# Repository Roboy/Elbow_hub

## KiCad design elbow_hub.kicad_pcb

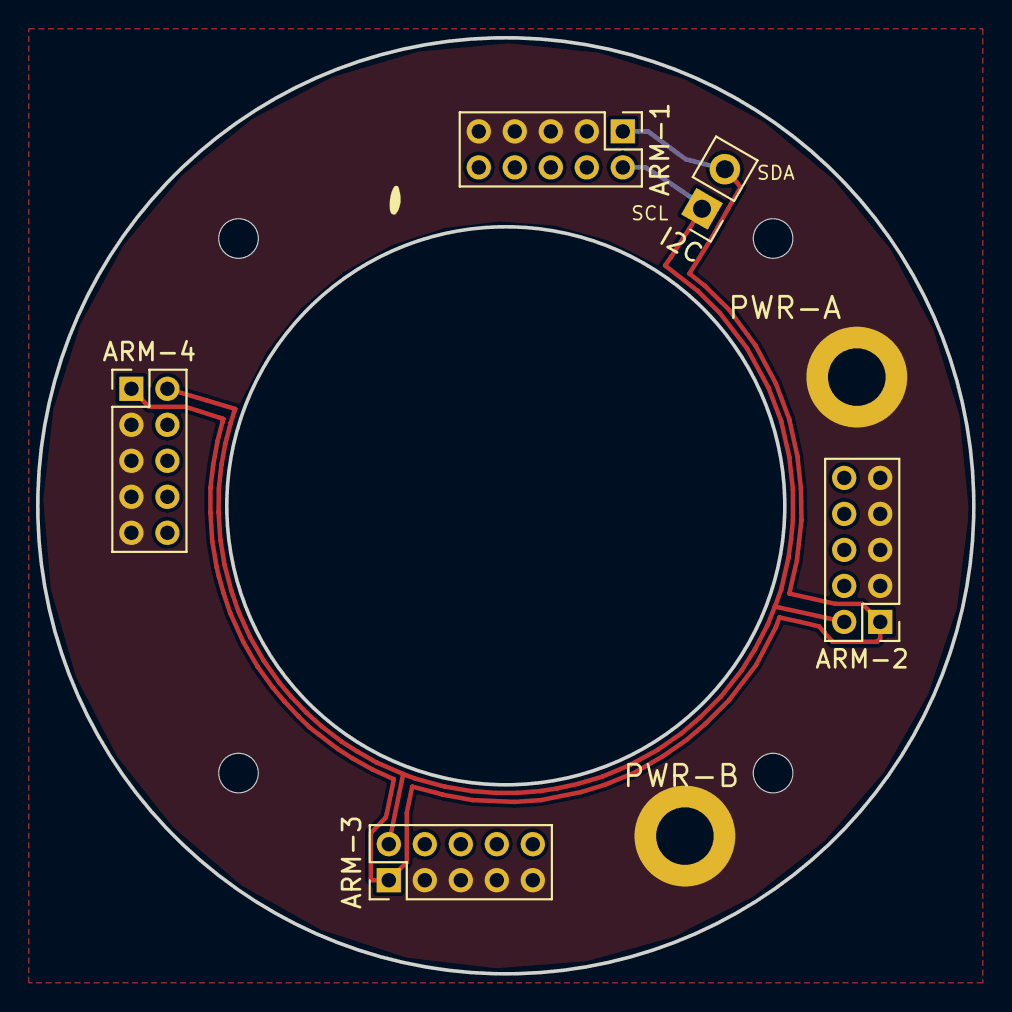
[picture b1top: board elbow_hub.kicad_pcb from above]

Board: 2 copper layers, 52.0 x 52.0 mm, 11 parts (0 on the bottom side), 4 nets.

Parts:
ARM-1, ARM-2, ARM-3, ARM-4: Conn_02x05_Odd_Even; PinHeader_2x05_P2.00mm_Vertical
I2C: Conn_01x02; PinHeader_1x02_P2.54mm_Vertical
MK1, MK2, MK3, MK4: M2; MountingHole_2.2mm_M2_DIN965
PWR-A: Conn_01x01; MountingHole_3.2mm_M3_DIN965_Pad
PWR-B: Conn_01x01; MountingHole_3.2mm_M3_DIN965_Pad

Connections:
+5V: ARM-1.4, ARM-1.6, ARM-1.8, ARM-1.10, ARM-2.4, ARM-2.6, ARM-2.8, ARM-2.10, ARM-3.4, ARM-3.6, ARM-3.8, ARM-3.10, ARM-4.4, ARM-4.6, ARM-4.8, ARM-4.10, PWR-A.1
/SCL: ARM-1.2, ARM-2.2, ARM-3.2, ARM-4.2, I2C.1
/SDA: ARM-1.1, ARM-2.1, ARM-3.1, ARM-4.1, I2C.2
GND: ARM-1.3, ARM-1.5, ARM-1.7, ARM-1.9, ARM-2.3, ARM-2.5, ARM-2.7, ARM-2.9, ARM-3.3, ARM-3.5, ARM-3.7, ARM-3.9, ARM-4.3, ARM-4.5, ARM-4.7, ARM-4.9, MK1.1, MK2.1, MK3.1, MK4.1, PWR-B.1

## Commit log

2018-02-03 First commit and already done\! \;\). All finished in one go, more or less ...
